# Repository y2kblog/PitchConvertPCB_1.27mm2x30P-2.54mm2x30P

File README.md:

# ピッチ変換基板(1.27mm 2×30P⇔2.54mm 2×30P)

## 概要
1.27mmピッチ2×30Pを2.54mmピッチ2×30P(300mil幅)に変換する基板です。

## 仕様
- ピンピッチ：1.27mm 2×30P ⇔ 2.54mm 2×30P
- 基板サイズ：10.16mm × 76.2mm
- 基板厚：1.6mm
- 基板色：緑
- 表面仕上げ：無鉛はんだ
- 両面スル―ホール
- 固定穴：70mmピッチ, φ3.2 × 2穴

## 販売  
[スイッチサイエンス委託販売ページ](https://www.switch-science.com/catalog/6862/)（ボックスヘッダ付）  
※大量注文や在庫に関する問い合わせは[こちら](mailto:info.y2kb@gmail.com)までご連絡ください。

## 寸法

## License
MIT License, see `/LICENSE`.

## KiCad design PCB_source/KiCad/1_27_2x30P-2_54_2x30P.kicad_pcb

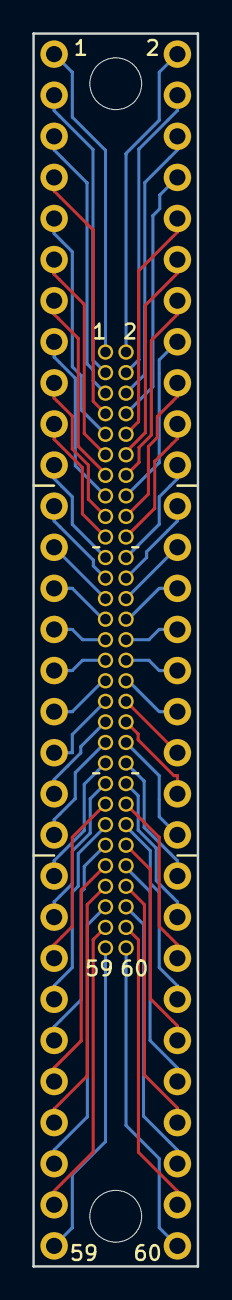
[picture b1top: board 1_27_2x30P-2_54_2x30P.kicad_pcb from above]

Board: 2 copper layers, 10.2 x 76.2 mm, 4 parts (0 on the bottom side), 60 nets.

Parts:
H1, H2: MountingHole; MountingHole_3.2mm_M3
J1: 1.27_2x30P; USER_DILhalf_30X2_NoSilk
J2: 2.54_2x30P; USER_DIL30X2_300milWidth_NoSilk

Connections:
/1: J1.1, J2.1
/2: J1.2, J2.2
/3: J1.3, J2.3
/4: J1.4, J2.4
/5: J1.5, J2.5
/6: J1.6, J2.6
/7: J1.7, J2.7
/8: J1.8, J2.8
/9: J1.9, J2.9
/10: J1.10, J2.10
/11: J1.11, J2.11
/12: J1.12, J2.12
/13: J1.13, J2.13
/14: J1.14, J2.14
/15: J1.15, J2.15
/16: J1.16, J2.16
/17: J1.17, J2.17
/18: J1.18, J2.18
/19: J1.19, J2.19
/20: J1.20, J2.20
/21: J1.21, J2.21
/22: J1.22, J2.22
/23: J1.23, J2.23
/24: J1.24, J2.24
/25: J1.25, J2.25
/26: J1.26, J2.26
/27: J1.27, J2.27
/28: J1.28, J2.28
/29: J1.29, J2.29
/30: J1.30, J2.30
/31: J1.31, J2.31
/32: J1.32, J2.32
/33: J1.33, J2.33
/34: J1.34, J2.34
/35: J1.35, J2.35
/36: J1.36, J2.36
/37: J1.37, J2.37
/38: J1.38, J2.38
/39: J1.39, J2.39
/40: J1.40, J2.40
/41: J1.41, J2.41
/42: J1.42, J2.42
/43: J1.43, J2.43
/44: J1.44, J2.44
/45: J1.45, J2.45
/46: J1.46, J2.46
/47: J1.47, J2.47
/48: J1.48, J2.48
/49: J1.49, J2.49
/50: J1.50, J2.50
/51: J1.51, J2.51
/52: J1.52, J2.52
/53: J1.53, J2.53
/54: J1.54, J2.54
/55: J1.55, J2.55
/56: J1.56, J2.56
/57: J1.57, J2.57
/58: J1.58, J2.58
/59: J1.59, J2.59
/60: J1.60, J2.60

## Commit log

2020-09-09 add files
2020-12-26 add switch science page link
